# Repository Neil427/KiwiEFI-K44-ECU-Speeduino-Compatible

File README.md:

# Speeduino-KiwiEFI-K44-ECU
The KiwiEFI K44 ECU is designed to run Speeduino firmware and is designed to be 100% compatible with the Speeduino V0.4 Mega2560 pin specification. 
In Tuner Studio select ecu type as V0.4.
  Features:
- 4 layer pcb for good noise immunity, reliable operation.
- 2x 24pin sealed automotive connectors.
- See specifications file for full details.

Open source design for those wishing to build from scratch.

Or will be available for purchase at www.kiwiefi.nz fully built up with mating loom connectors, (firmware/base tune loaded and tested on a real engine) . 

If you would like to save some freight costs and purchase just the pcb fitted with all smd components only (i.e. less box, connectors, arduino, and all other throughhole components) please contact me through www.kiwiefi.nz

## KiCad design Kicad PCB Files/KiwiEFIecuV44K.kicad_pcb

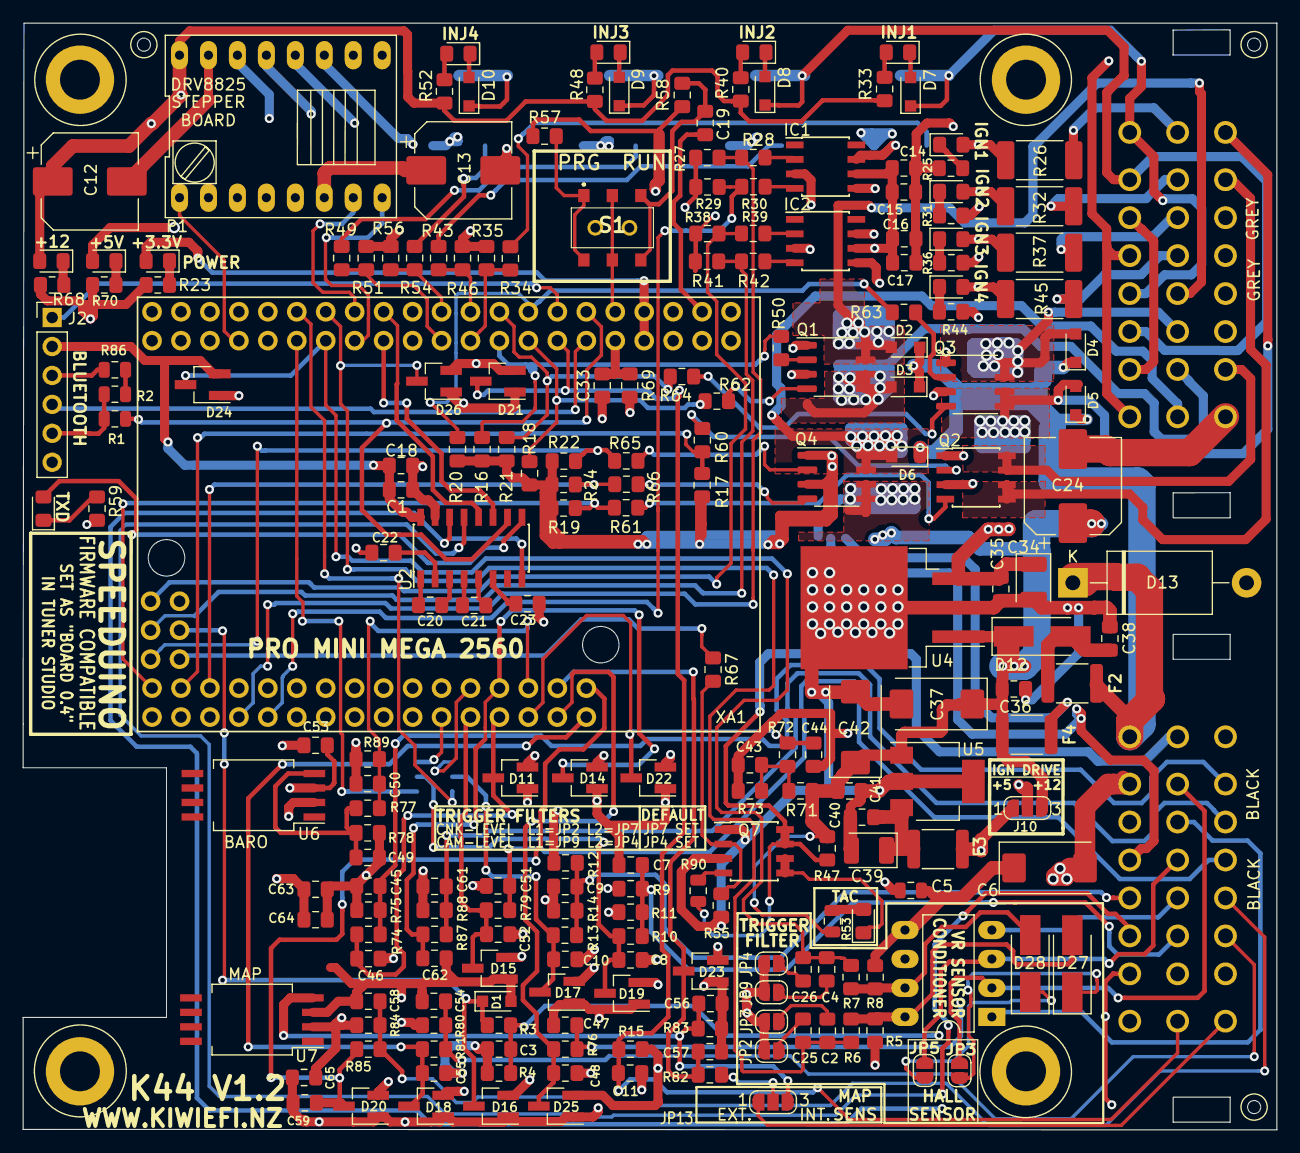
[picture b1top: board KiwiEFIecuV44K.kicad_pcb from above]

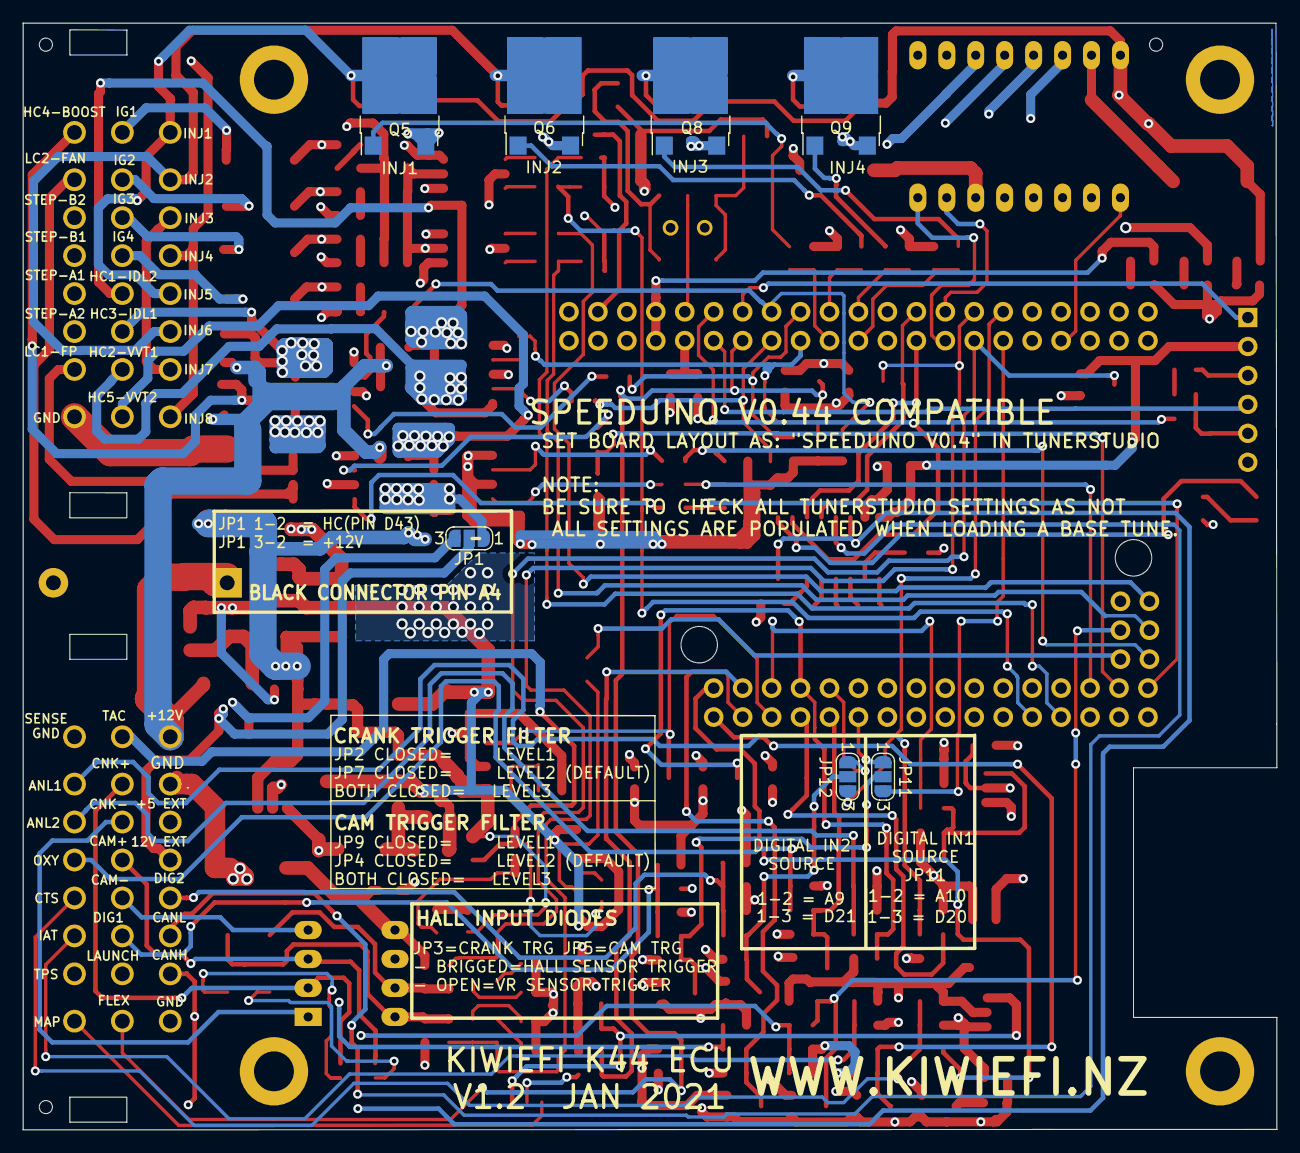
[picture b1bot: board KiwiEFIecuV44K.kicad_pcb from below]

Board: 4 copper layers, 110.0 x 97.1 mm, 228 parts (7 on the bottom side), 157 nets.

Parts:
C1, C20, C21, C22, C23, C33, C63, C65: 1uF; C_0805_2012Metric_Pad1.15x1.40mm_HandSolder
C2, C4: 10n; C_0805_2012Metric_Pad1.15x1.40mm_HandSolder
C3, C7, C9, C14, C16, C43, C45, C47, C51, C54, C58, C61: u1; C_0805_2012Metric_Pad1.15x1.40mm_HandSolder
C5: 0.1uF; C_0805_2012Metric
C6, C37, C42: 10uF; CP_EIA-7343-31_Kemet-D
C8, C10, C11, C44, C48, C52, C55, C59: u22; C_0805_2012Metric_Pad1.15x1.40mm_HandSolder
C12, C13: 100uF 35V; CP_Elec_8x10
C15, C17: 1u; C_0805_2012Metric_Pad1.15x1.40mm_HandSolder
C18, C53, C64: 100n; C_0805_2012Metric_Pad1.15x1.40mm_HandSolder
C19: 22uF; C_0805_2012Metric_Pad1.15x1.40mm_HandSolder
C24: 220uF25V; CP_Elec_8x10
C25: 4n7; C_0805_2012Metric_Pad1.15x1.40mm_HandSolder
C26: 22n; C_0805_2012Metric_Pad1.15x1.40mm_HandSolder
C34, C39: 47uF; CP_EIA-3528-21_Kemet-B
C35, C36, C38, C40, C41: 0.1uF; C_0805_2012Metric_Pad1.15x1.40mm_HandSolder
C46, C50, C57, C62: u33; C_0805_2012Metric_Pad1.15x1.40mm_HandSolder
C49, C56: 47p; C_0805_2012Metric_Pad1.15x1.40mm_HandSolder
D1: MM3Z5V1ST1G; D_SOD-323_HandSoldering
D2, D3, D4, D5, D6, D7, D8, D9, D10: 1N4448WX-TP; D_SOD-323_HandSoldering
D11, D14, D15, D16, D17, D18, D19, D20, D21, D22, D23, D24, D25, D26: BAT54S; SOT-23_BAT54S
D12, D27, D28: B130-13-F; D_SMA_Handsoldering
D13: MR2535L; D_DO-201AE_P15.24mm_Horizontal
F2: 0.5A; Fuse_1812_4532Metric
F3, F4: 0.25A; Fuse_1812_4532Metric
IC1, IC2: TC4424A; SOIC-8_3.9x4.9mm_P1.27mm
J1: Conn_02x24_Male; Delphi_48pinConnectorBox_AandBconnectors
J2: BLUETOOTH 1 tx/rx0; PinHeader_1x06_P2.54mm_Vertical
J3, J4, J6: TOOLING HOLE; ToolingHole
J5: TRIGGER CONDITIONER; DIP-8_W7.62mm_LongPads
J10: IGNITER PULLUP 5V/12V; SolderJumper-3_P1.3mm_Open_RoundedPad1.0x1.5mm_NumberLabels
JP1: EXT 12V EN; SolderJumper-3_P1.3mm_Open_RoundedPad1.0x1.5mm_NumberLabels
JP2: CNK_FILTER-2; SolderJumper-2_P1.3mm_Open_RoundedPad1.0x1.5mm
JP3: HALL-CNK; SolderJumper-2_P1.3mm_Open_RoundedPad1.0x1.5mm
JP4: CAM_FILTER-2; SolderJumper-2_P1.3mm_Open_RoundedPad1.0x1.5mm
JP5: HALL-CAM; SolderJumper-2_P1.3mm_Open_RoundedPad1.0x1.5mm
JP7: CNK_FILTER-1; SolderJumper-2_P1.3mm_Open_RoundedPad1.0x1.5mm
JP9: CAM_FILTER-1; SolderJumper-2_P1.3mm_Open_RoundedPad1.0x1.5mm
JP11: DIGITAL1 SEL; SolderJumper-3_P1.3mm_Open_RoundedPad1.0x1.5mm_NumberLabels
JP12: DIGITAL2 SEL; SolderJumper-3_P1.3mm_Open_RoundedPad1.0x1.5mm_NumberLabels
JP13: IGN8; SolderJumper-3_P1.3mm_Open_RoundedPad1.0x1.5mm_NumberLabels
LED1, LED2, LED3, LED4, LED5, LED6, LED7, LED8, LED10, LED11, LED12, LED13: GREEN; LED_0805_2012Metric_Pad1.15x1.40mm_HandSolder
LED9: BLUE TAC LED; LED_0805_2012Metric_Pad1.15x1.40mm_HandSolder
P1: DRV8825; DRV8825_STEPPER
Q1, Q3, Q4: VNS3NV04D; SO-8_3.9x4.9mm_P1.27mm
Q2, Q7: NCV8402AD; SOIC-8_3.9x4.9mm_P1.27mm
Q5, Q6, Q8, Q9: NCV8408; ATPAK-2
R1, R2, R86: 1K; R_0805_2012Metric
R3: 1K; C_0805_2012Metric_Pad1.15x1.40mm_HandSolder
R4, R11, R14, R16, R17, R18, R19, R20, R21, R22, R24, R27, R29, R35, R38, R41, R46, R51, R55, R56: 51K; C_0805_2012Metric_Pad1.15x1.40mm_HandSolder
R5, R8, R9, R12, R25, R28, R30, R31, R33, R34, R36, R39, R40, R42, R43, R44, R47, R48, R49, R52, R54, R59: 1K; R_0805_2012Metric_Pad1.15x1.40mm_HandSolder
R6, R7, R67: 220R; C_0805_2012Metric_Pad1.15x1.40mm_HandSolder
R10, R13, R72, R74, R76, R77, R79, R81, R82, R85, R87: 470r; C_0805_2012Metric_Pad1.15x1.40mm_HandSolder
R15: 2K49; C_0805_2012Metric_Pad1.15x1.40mm_HandSolder
R23: 2K2; R_0805_2012Metric_Pad1.15x1.40mm_HandSolder
R26, R32, R37, R45: 10R; R_2512_6332Metric_Pad1.52x3.35mm_HandSolder
R50, R60, R61, R62, R63, R64, R65, R66: 220R; R_0805_2012Metric_Pad1.15x1.40mm_HandSolder
R53, R90: 10K; R_0805_2012Metric
R57: 10k; R_0805_2012Metric_Pad1.15x1.40mm_HandSolder
R58: 120R; R_0805_2012Metric_Pad1.15x1.40mm_HandSolder
R68, R69: 10K; R_0805_2012Metric_Pad1.15x1.40mm_HandSolder
R70: 3K9; R_0805_2012Metric_Pad1.15x1.40mm_HandSolder
R71: 3k9; C_0805_2012Metric_Pad1.15x1.40mm_HandSolder
R73: 1k; C_0805_2012Metric_Pad1.15x1.40mm_HandSolder
R75, R78, R83, R88: 51k; C_0805_2012Metric_Pad1.15x1.40mm_HandSolder
R80, R84: 2k49; C_0805_2012Metric_Pad1.15x1.40mm_HandSolder
R89: 1M; C_0805_2012Metric_Pad1.15x1.40mm_HandSolder
S1: RESET SEL; AYZ0202AGRLC
U2: MAX232; SOIC-16_3.9x9.9mm_P1.27mm
U4: LM2940IMP-5.0/NOPB; TO-263-3_TabPin2
U5: LM2940IMP-5.0/NOPB; SOT-223-3_TabPin2
U6: MPXHZ6115A; SSO-8_6.8x5.9mm_P1.27mm_Clearance8mm
U7: MPXHZ6400A; SSO-8_6.8x5.9mm_P1.27mm_Clearance8mm
XA1: Arduino_Mega_Mini; Arduino_Mega2560_ProMini

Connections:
5V-EXT: F3.2, J1.a3, J10.1
12V-EXT: F4.2, JP1.3
+3.3V: LED11.2, XA1.3V3_1, XA1.3V3_2
+5C: C14.1, C15.1, C16.1, C17.1, IC1.6, IC2.6, J10.2
+5V: C1.1, C5.1, C6.1, C13.1, C18.1, C22.1, C34.1, C35.1, C53.1, C63.1, C64.1, C65.1, D11.2, D14.2, D15.2, D16.2, D17.2, D18.2, D19.2, D20.2, D21.2, D22.2, D23.2, D24.2, D25.2, D26.2, J2.2, J5.5, LED12.2, P1.5, P1.6, R5.1, R8.2, R9.2, R12.2, R15.1, R57.1, R58.2, R69.2, R80.1, R84.1, U2.16, U4.3, U6.2, U7.2, XA1.5V_1, XA1.5V_2
+12V: C12.1, C24.1, C36.1, C37.1, C41.1, C42.1, D12.1, F4.1, J10.3, LED13.2, P1.16, R33.1, R40.1, R47.2, R48.1, R52.1, R53.2, R71.1, U4.1, U5.1
+Vflyback: D2.1, D3.1, D4.1, D5.1, D6.1, D13.1, F2.2, J1.a1
A9-MCU: JP12.1, XA1.A9
A10-MCU: JP11.1, XA1.A10
ANALOG1: C45.2, J1.a18, R74.2, R75.2
ANALOG1-MCU: C46.2, D11.3, R74.1, XA1.A6
ANALOG2: C61.2, J1.a19, R87.2, R88.2
ANALOG2-MCU: C62.2, D14.3, R87.1, XA1.A7
BARO-MCU: C50.2, R77.1, R89.2, XA1.A5
BAT-MCU: C44.1, D22.3, R72.2, XA1.A4
BOOST: D5.2, J1.b17, Q3.5, Q3.6
CAM: J1.a12, J5.3, JP5.1
CAM-MCU: C4.1, C26.2, D24.3, R7.2, XA1.D18
CLAMP3: C52.1, D15.3, R79.2, XA1.A8
CLAMP4: C10.1, D17.3, JP12.2, R13.2
CLAMP5: C8.1, D19.3, JP11.2, R10.2
CLAMP6: C11.1, D21.3, J1.a16, R15.2, XA1.D2
CLAMP7: C57.2, D23.3, R82.1, XA1.A3
CLAMP8: C48.1, D25.3, R76.2, XA1.A2
CLAMP9: D1.1, D16.3, R3.2, XA1.D51
CLAMP10: C55.1, D18.3, R81.2, XA1.A0
CLAMP11: C59.1, D20.3, R85.2, XA1.A1
CLAMP14: C2.2, C25.2, D26.3, R6.2, XA1.D19
CLT: C58.1, J1.a21, R84.2, R85.1
CRANK: J1.a10, J5.2, JP3.1
D0-MCU: J2.4, XA1.D0
D1-MCU: R1.1, U2.10, XA1.D1
D1bt-MCU: J2.5, R1.2, R2.1
D3-MCU: J2.1, XA1.D3
D20-MCU: JP11.3, XA1.D20
D21-MCU: JP12.3, XA1.D21
D43OUT: R24.2, R66.1, XA1.D43
DIGITAL1: C7.1, J1.a14, R9.1, R10.1, R11.1
DIGITAL2: C9.1, J1.a5, R12.1, R13.1, R14.1
DIR-MCU: P1.8, XA1.D16
EN-MCU: P1.1, XA1.D24
FAN1: J1.b18, Q2.5, Q2.6
FP: J1.b23, Q2.7, Q2.8
GND: C1.2, C3.2, C5.2, C6.2, C7.2, C8.2, C9.2, C10.2, C11.2, C12.2, C13.2, C14.2, C15.2, C16.2, C17.2, C18.2, C19.2, C23.1, C24.2, C33.1, C34.2, C35.2, C36.2, C37.2, C38.2, C39.2, C40.2, C41.2, C42.2, C43.2, C44.2, C45.1, C46.1, C47.2, C48.2, C49.1, C50.1, C51.2, C52.2, C53.2, C54.2, C55.2, C56.1, C57.1, C58.2, C59.2, C61.1, C62.1, C63.2, C64.2, C65.2, D1.2, D11.1, D13.2, D14.1, D15.1, D16.1, D17.1, D18.1, D19.1, D20.1, D21.1, D22.1, D23.1, D24.1, D25.1, D26.1, IC1.3, IC2.3, J1.a2, J1.a8, J1.a17, J1.b24, J2.3, J5.6, JP2.2, JP4.2, JP7.2, JP9.2, P1.9, P1.15, Q1.1, Q1.3, Q2.1, Q2.3, Q3.1, Q3.3, Q4.1, Q4.3, Q5.3, Q6.3, Q7.1, Q7.3, Q8.3, Q9.3, R4.2, R11.2, R14.2, R16.1, R17.1, R18.1, R19.1, R20.1, R21.1, R22.1, R23.2, R24.1, R25.2, R27.2, R29.1, R31.2, R35.1, R36.2, R38.2, R41.1, R44.2, R46.1, R51.1, R55.1, R56.1, R59.2, R68.2, R70.2, R73.1, R75.1, R78.1, R83.1, R86.1, R88.1, R89.1, U2.15, U4.2, U5.2, U6.3, U7.3, XA1.GND1, XA1.GND2
HC1-MCU: R16.2, R50.2, XA1.D6
HC2-MCU: R18.2, R62.2, XA1.D4
HC3-MCU: R20.2, R63.2, XA1.D5
HC4-MCU: R21.2, R64.2, XA1.D7
HC5-MCU: R22.2, R65.2, XA1.D48
HCD43: JP1.1, Q4.5, Q4.6
IAT: C54.1, J1.a22, R80.2, R81.1
IDL1: D4.2, J1.b14, Q3.7, Q3.8
IDL2: D2.2, J1.b13, Q1.7, Q1.8
IGN1: J1.b9, R26.1
IGN1-MCU: R27.1, R28.2, XA1.D40
IGN2: J1.b10, R32.1
IGN2-MCU: R29.2, R30.2, XA1.D38
IGN3: J1.b11, R37.1
IGN3-MCU: R38.1, R39.2, XA1.D52
IGN4: J1.b12, R45.1
IGN4-MCU: R41.2, R42.2, XA1.D50
INJ1: D7.1, J1.b1, J1.b5, Q5.2
INJ1-MCU: R34.2, R35.2, XA1.D8
INJ2: D8.1, J1.b2, J1.b6, Q6.2
INJ2-MCU: R43.2, R46.2, XA1.D9
INJ3: D9.1, J1.b3, J1.b7, Q8.2
INJ3-MCU: R49.2, R51.2, XA1.D10
INJ4: D10.1, J1.b4, J1.b8, Q9.2
INJ4-MCU: R54.2, R56.2, XA1.D11
LAUNCH: C3.1, J1.a15, R3.1, R4.1
LC1-MCU: R17.2, R60.1, XA1.D45
LC2-MCU: R19.2, R61.1, XA1.D47
LC3-MCU: R67.1, XA1.D49
MAP-EXT: J1.a24, JP13.1
unnamed: C2.1, JP7.1
unnamed: C4.2, JP9.1
unnamed: C19.1, R58.1, S1.3, S1.6
unnamed: C20.1, U2.1
unnamed: C20.2, U2.3
unnamed: C21.1, U2.4
unnamed: C21.2, U2.5
unnamed: C22.2, U2.2
unnamed: C23.2, U2.6
unnamed: C25.1, JP2.1
unnamed: C26.1, JP4.1
unnamed: C33.2, R69.1, XA1.AREF
unnamed: C38.1, D12.2, F2.1
unnamed: C39.1, C40.1, F3.1, U5.3
unnamed: C43.1, R71.2, R72.1, R73.2
unnamed: C49.2, R77.2, R78.2, U6.4
unnamed: C56.2, JP13.3, R83.2, U7.4
unnamed: D7.2, LED3.1
unnamed: D8.2, LED5.1
unnamed: D9.2, LED7.1
unnamed: D10.2, LED8.1
unnamed: D27.1, JP3.2
unnamed: D27.2, J5.8, R5.2, R6.1
unnamed: D28.1, JP5.2
unnamed: D28.2, J5.7, R7.1, R8.1
unnamed: IC1.2, R28.1
unnamed: IC1.4, R30.1
unnamed: IC1.5, LED2.2, R32.2
unnamed: IC1.7, LED1.2, R26.2
unnamed: IC2.2, R39.1
unnamed: IC2.4, R42.1
unnamed: IC2.5, LED6.2, R45.2
unnamed: IC2.7, LED4.2, R37.2
unnamed: J1.a4, JP1.2
unnamed: JP13.2, R82.2
unnamed: LED1.1, R25.1
unnamed: LED2.1, R31.1
unnamed: LED3.2, R33.2
unnamed: LED4.1, R36.1
unnamed: LED5.2, R40.2
unnamed: LED6.1, R44.1
unnamed: LED7.2, R48.2
unnamed: LED8.2, R52.2
unnamed: LED9.1, Q7.5, Q7.6
unnamed: LED9.2, R53.1
unnamed: LED10.1, R59.1
unnamed: LED10.2, U2.9
unnamed: LED11.1, R23.1
unnamed: LED12.1, R70.1
unnamed: LED13.1, R68.1
unnamed: Q1.2, R50.1
unnamed: Q1.4, R62.1
unnamed: Q2.2, R60.2
unnamed: Q2.4, R61.2
unnamed: Q3.2, R63.1
unnamed: Q3.4, R64.1
unnamed: Q4.2, R65.1
unnamed: Q4.4, R66.2
unnamed: Q5.1, R34.1
unnamed: Q6.1, R43.1
unnamed: Q7.2, R55.2, R67.2
unnamed: Q7.4, R90.1
unnamed: Q8.1, R49.1
unnamed: Q9.1, R54.1
unnamed: R2.2, R86.2
unnamed: R57.2, S1.1, S1.4
unnamed: S1.2, S1.5, XA1.RST
O2: C51.1, J1.a20, R79.1
RX3C: J1.a6, U2.13
RXD3-MCU: U2.12, XA1.D15
SPAREout1: D6.2, J1.b16, Q4.7, Q4.8
STEP-A1: J1.b21, P1.12
STEP-A2: J1.b22, P1.11
STEP-B1: J1.b20, P1.13
STEP-B2: J1.b19, P1.14
STEP-MCU: P1.7, XA1.D17
TACH: J1.a9, Q7.7, Q7.8, R47.1, R90.2
TPS: C47.1, J1.a23, R76.1
TX3C: J1.a7, U2.8, U2.14
TXD3-MCU: U2.11, XA1.D14
VR1-: J1.a11, J5.1
VR2-: J1.a13, J5.4
VVT: D3.2, J1.b15, Q1.5, Q1.6

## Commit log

2022-07-07 Add files via upload
    Added files for V1.2
2023-04-23 Added PickAndPlace file
2023-05-13 Add files via upload
    Updated
